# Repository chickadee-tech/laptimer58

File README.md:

# chickadee-laptimer-pcb
PCB design files for Chickadee Lap Timer.

See subfolders for licenses. Code is typically MIT Licensed and PCB designs are typically Creative Commons BY-SA.

Kicad files use components available in https://github.com/chickadee-tech/kicad-libs. It is assumed that this directory is ../shared/kicad/libraries/public/ relative to the root of this repository. You may find absolute paths that still need to be fixed. Please provide a pull request to fix those.

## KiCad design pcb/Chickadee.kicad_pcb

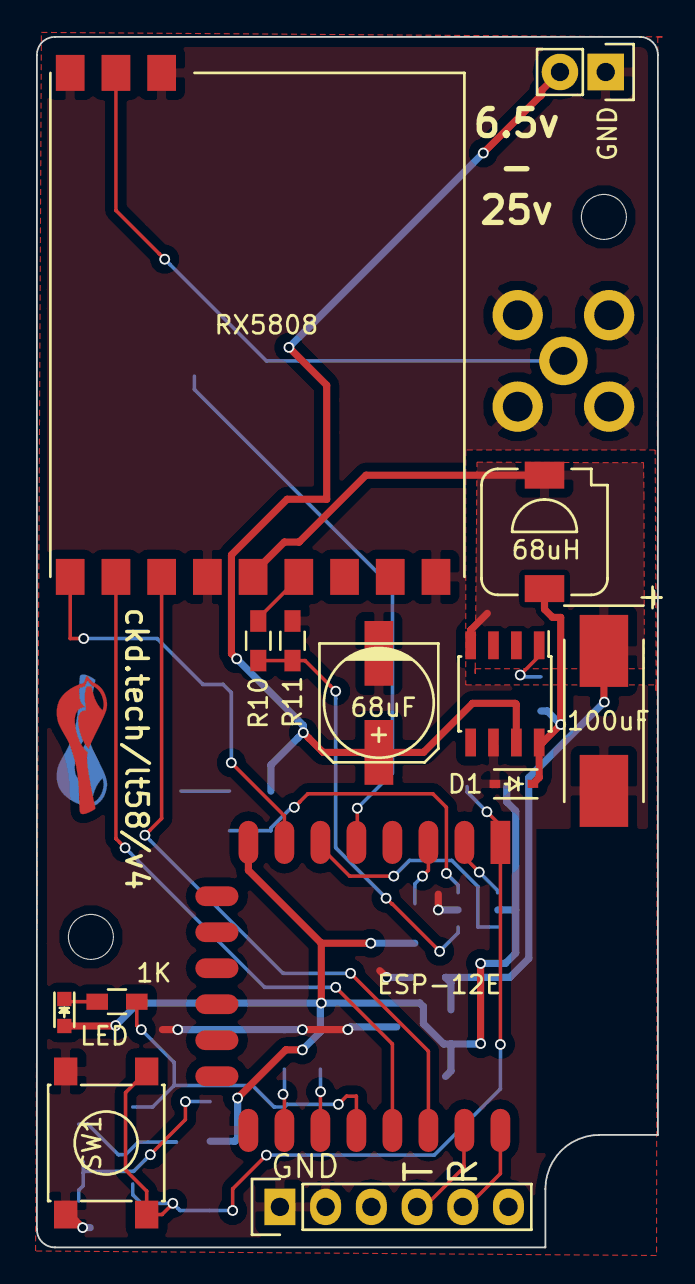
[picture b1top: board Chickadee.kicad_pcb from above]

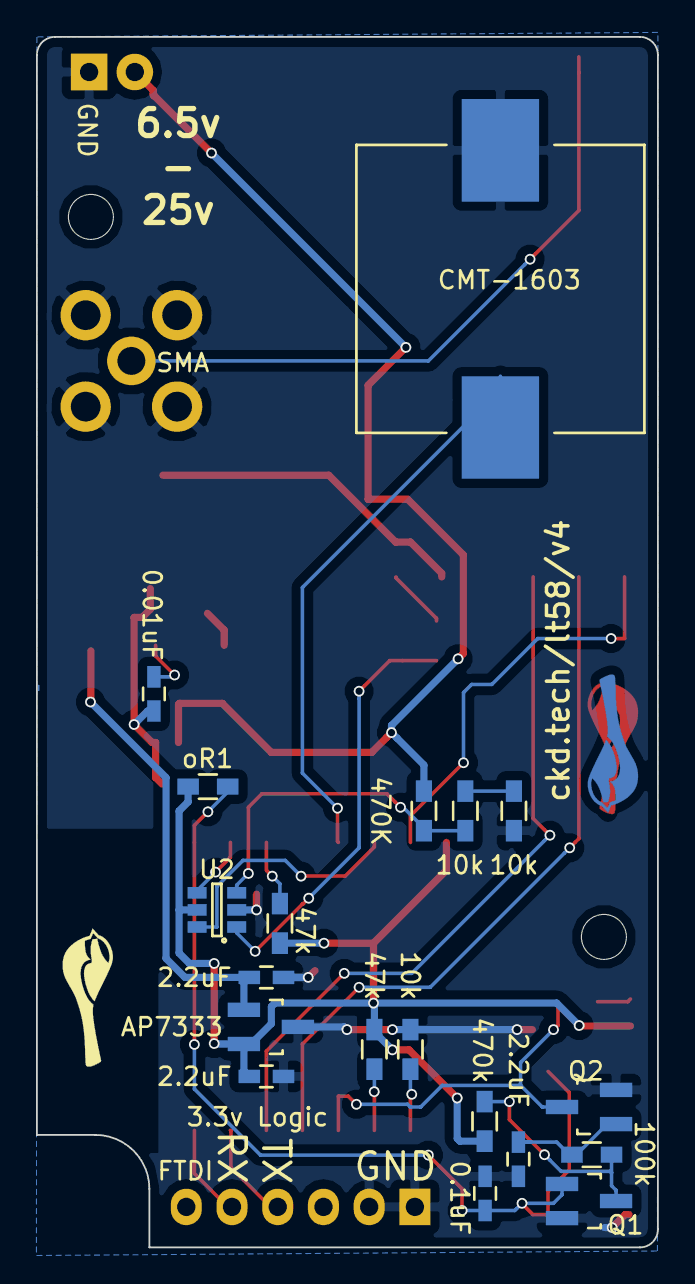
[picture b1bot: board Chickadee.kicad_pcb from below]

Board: 2 copper layers, 34.5 x 67.2 mm, 34 parts (19 on the bottom side), 27 nets.

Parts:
C1: 0.1uF; C_0603_HandSoldering
C2, C3, C4: 2.2uF; C_0603_HandSoldering
CB1: 0.01uF; C_0603_HandSoldering
Cin1: 68uF; c_elec_6.3x7.7
Cout1: 100uF; TantalC_SizeD_EIA-7343_HandSoldering
D1: SD103BWS-TP; SOD-323
D2: LED; LED-0603
J1: SMA; SMA-Jack-Straight
L1: 68uH; SLF7032
LS1: CMT-1603; CMT-1603-SMT
P1: FTDI; Pin_Header_Straight_1x06
P2: CONN_01X02; Pin_Header_Straight_1x02
Q1, Q2: Q_NMOS_GSD; SOT-23_Handsoldering
R1: 470k; R_0603_HandSoldering
R2: 100k; R_0603_HandSoldering
R3, R5: 47k; R_0603_HandSoldering
R4: 1K; R_0603_HandSoldering
R6, R8, R9, R11: 10k; R_0603_HandSoldering
R7: 470K; R_0603_HandSoldering
R10: 1k; R_0603_HandSoldering
RF1: RX5808; rx5808
SW1: SW_PUSH; SW_SPST_PTS645
U1: ESP-12E
U2: 74LVC1G3157; SOT-23-6
U3: LM2674M-3.3; SOIC-8_3.9x4.9mm_Pitch1.27mm
U4: AP7333; SOT-23_Handsoldering
oR1: 10k; R_0603_HandSoldering

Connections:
+3V3: C4.1, D2.2, R1.1, R3.2, R5.1, U1.8, U2.5, U4.2, oR1.1
+5V: C3.1, Cout1.1, L1.1, RF1.8, U3.4, U4.1
+BATT: Cin1.1, P2.2, R7.1, U3.7
/5V/3V3 Regulator/5uf: CB1.2, D1.1, L1.2, U3.8
/ADC_SELECT: U1.6, U2.6
/CLK: RF1.6, U1.20
/DATA: RF1.4, U1.7
/ESP-Reset/GPIO0: Q2.3, R4.2, U1.18
/ESP-Reset/RESET: C1.1, Q1.1, SW1.2, U1.1, oR1.2
/LE: RF1.5, U1.19
/RFIN: J1.1, RF1.2
/RSSI: R10.1, RF1.9
/RXI: P1.5, U1.22
/SHARED_ADC: U1.2, U2.4
/TXO: P1.4, U1.21
GNDPWR: C1.2, C2.2, C3.2, C4.2, Cin1.2, Cout1.2, D1.2, J1.2, J1.3, J1.4, J1.5, LS1.2, P1.1, P1.2, P2.1, Q1.2, Q2.2, R6.1, R9.2, R11.2, RF1.1, RF1.3, RF1.7, RF1.12, SW1.1, U1.15, U2.2, U3.6, U4.3
unnamed: C2.1, Q2.1, R2.1
unnamed: CB1.1, U3.1
unnamed: D2.1, R4.1
unnamed: LS1.1, U1.5
unnamed: Q1.3, R1.2, R2.2
unnamed: R3.1, U1.3
unnamed: R5.2, U1.17
unnamed: R6.2, U1.16
unnamed: R7.2, R8.1, U2.3
unnamed: R8.2, R9.1
unnamed: R10.2, R11.1, U2.1

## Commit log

2015-11-08 Add 'laptimer/' from commit 'ad23e0cf0ae844a5073d6c5f4a7300dd6b9fdc45'
    git-subtree-dir: laptimer
    git-subtree-mainline: d5137dc4f598fd388e51b94a87d69fd50ee67068
    git-subtree-split: ad23e0cf0ae844a5073d6c5f4a7300dd6b9fdc45
2015-11-08 Add 'laptimer/firmware/' from commit 'ff3d33ced65654df5b03affcefb19a7e25244b36'
    git-subtree-dir: laptimer/firmware
    git-subtree-mainline: fcb14fdbdfc2571a81df16ad77ce392b93cbcd22
    git-subtree-split: ff3d33ced65654df5b03affcefb19a7e25244b36
2015-11-08 Laptimer PCB firmware.
2015-11-08 Add 'laptimer/tools/log_analysis/' from commit 'c05ad9e7786d40f8d711c20d9a6ed2dc90feb600'
    git-subtree-dir: laptimer/tools/log_analysis
    git-subtree-mainline: 7574998d6e02a5272a75e4a79d0b8d64e1a74f9c
    git-subtree-split: c05ad9e7786d40f8d711c20d9a6ed2dc90feb600
2015-11-08 Add 'laptimer/apps/iOS/' from commit '63c4670ec9550a2d02d119fcb4d7d4f82399f977'
    git-subtree-dir: laptimer/apps/iOS
    git-subtree-mainline: de4596f8893afb4d925d30a7a27eda7d49277136
    git-subtree-split: 63c4670ec9550a2d02d119fcb4d7d4f82399f977
2015-11-08 Move pcb files to their own directory.
2015-11-08 Consolidate gitignore
2015-11-08 Shuffle around libraries so they are more easily shared.
2015-11-17 Update the Laptimer firmware code for PCB v3
2015-11-17 Update Laptimer iOS app for its new location.
2015-11-17 Move gerber folder
2015-11-18 v4 of laptimer with everything connected and RSSI voltage divider.
2015-11-27 Get TCP connections back from the Chickadee.
2015-12-01 Have the AP ESP forward packets from the other. Also batch individual readings into larger TCP packets.
2015-12-04 Split up the python client for the laptimers into separate functions with the hope of having live graphs. They don't work on OSX though. :-/
2015-12-04 Touched the pcb files with a new version of Kicad.
2015-12-04 Change the laptimer firmware so that all data is forwarded through the designated AP.
2015-12-07 Debugging the rssi value.
2015-12-07 tweaks to pcb
2015-12-07 Support json logged files rather than the binary format used in the first breadboarded version.
2015-12-07 Print the first value received in each group to get a glimpse of the data being recorded.
2015-12-07 Add licenses and a little more explanation.
2015-12-14 Update to react native 0.16. Needs https://github.com/naoufal/react-native-speech/pull/10 applied to react-native-speech.
2015-12-15 Get data working over TCP to the iOS app by having the AP node host a TCP server. Also change the Python client to behave in the same way.
2015-12-15 Correct READMEs mention of license.
2015-12-17 Introduce a replay.js script to run sample analysis on a previously recorded file. It will also render a plot of the data for debugging.
2015-12-17 Add peak detection and trigger speech based on it. Also add a replay server that serves data to the app in real-time.
2015-12-18 Add logging of all devices to a single file and get it working on a real phone.
